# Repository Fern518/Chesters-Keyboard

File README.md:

# Chester's Keyboard
A custom TKL keyboard built for the *Hack Club Blueprint program*.

It functions as a miniature media dashboard: the display shows the current track (TO BE IMPLEMENTED), the knob controls volume, and the six keys can be bound to any shortcut.

## The Keyboard
Everything fits together using 4 M3 Bolts and Heatset inserts, one in each corner. 

It has 2 separate printed pieces. The base, where the PCB sits, and the top cover, which protects the PCB.

## PCB
My PCB was designed in KiCad. The rPi Pico is mounted on the bottom of the PCB between the home keys and arrow keys to make it as compact as possible.

Schematic:

PCB:

## BOM:
- 1x Case 
- 1x [Raspberry Pi Pico 2W](https://www.adafruit.com/pico?src=raspberrypi)
- 1x [0.91" 128x32 OLED Display](https://www.addicore.com/products/oled-display-128x32-0-91in-monochrome?variant=45759649120573)
- 1x [1N4148 Diodes - 100 Pack](https://www.adafruit.com/product/5099)
- 1x [EC11 Rotary Encoder](https://www.aliexpress.us/item/3256805924910339.html)
- 1x PCB (gerber files in pcb/)
- 89x [Cherry MX Switches](https://a.co/d/hjQgWfm)
- 89x [Keycaps](https://mechanicalkeyboards.com/products/tai-hao-104-key-pbt-double-shot-keycap-set-dark-greyblack)
- 1x [Keycap Stabilizers pack](https://divinikey.com/products/aeboards-staebies-v2-stabilizers?variant=40005101355073)
- 1x [Adafruit MCP23017 I2C GPIO Expander Breakout](https://www.adafruit.com/product/5346)
- 4x M3x5x4 Heatset inserts
- 4x M3x16mm SHCS Bolts

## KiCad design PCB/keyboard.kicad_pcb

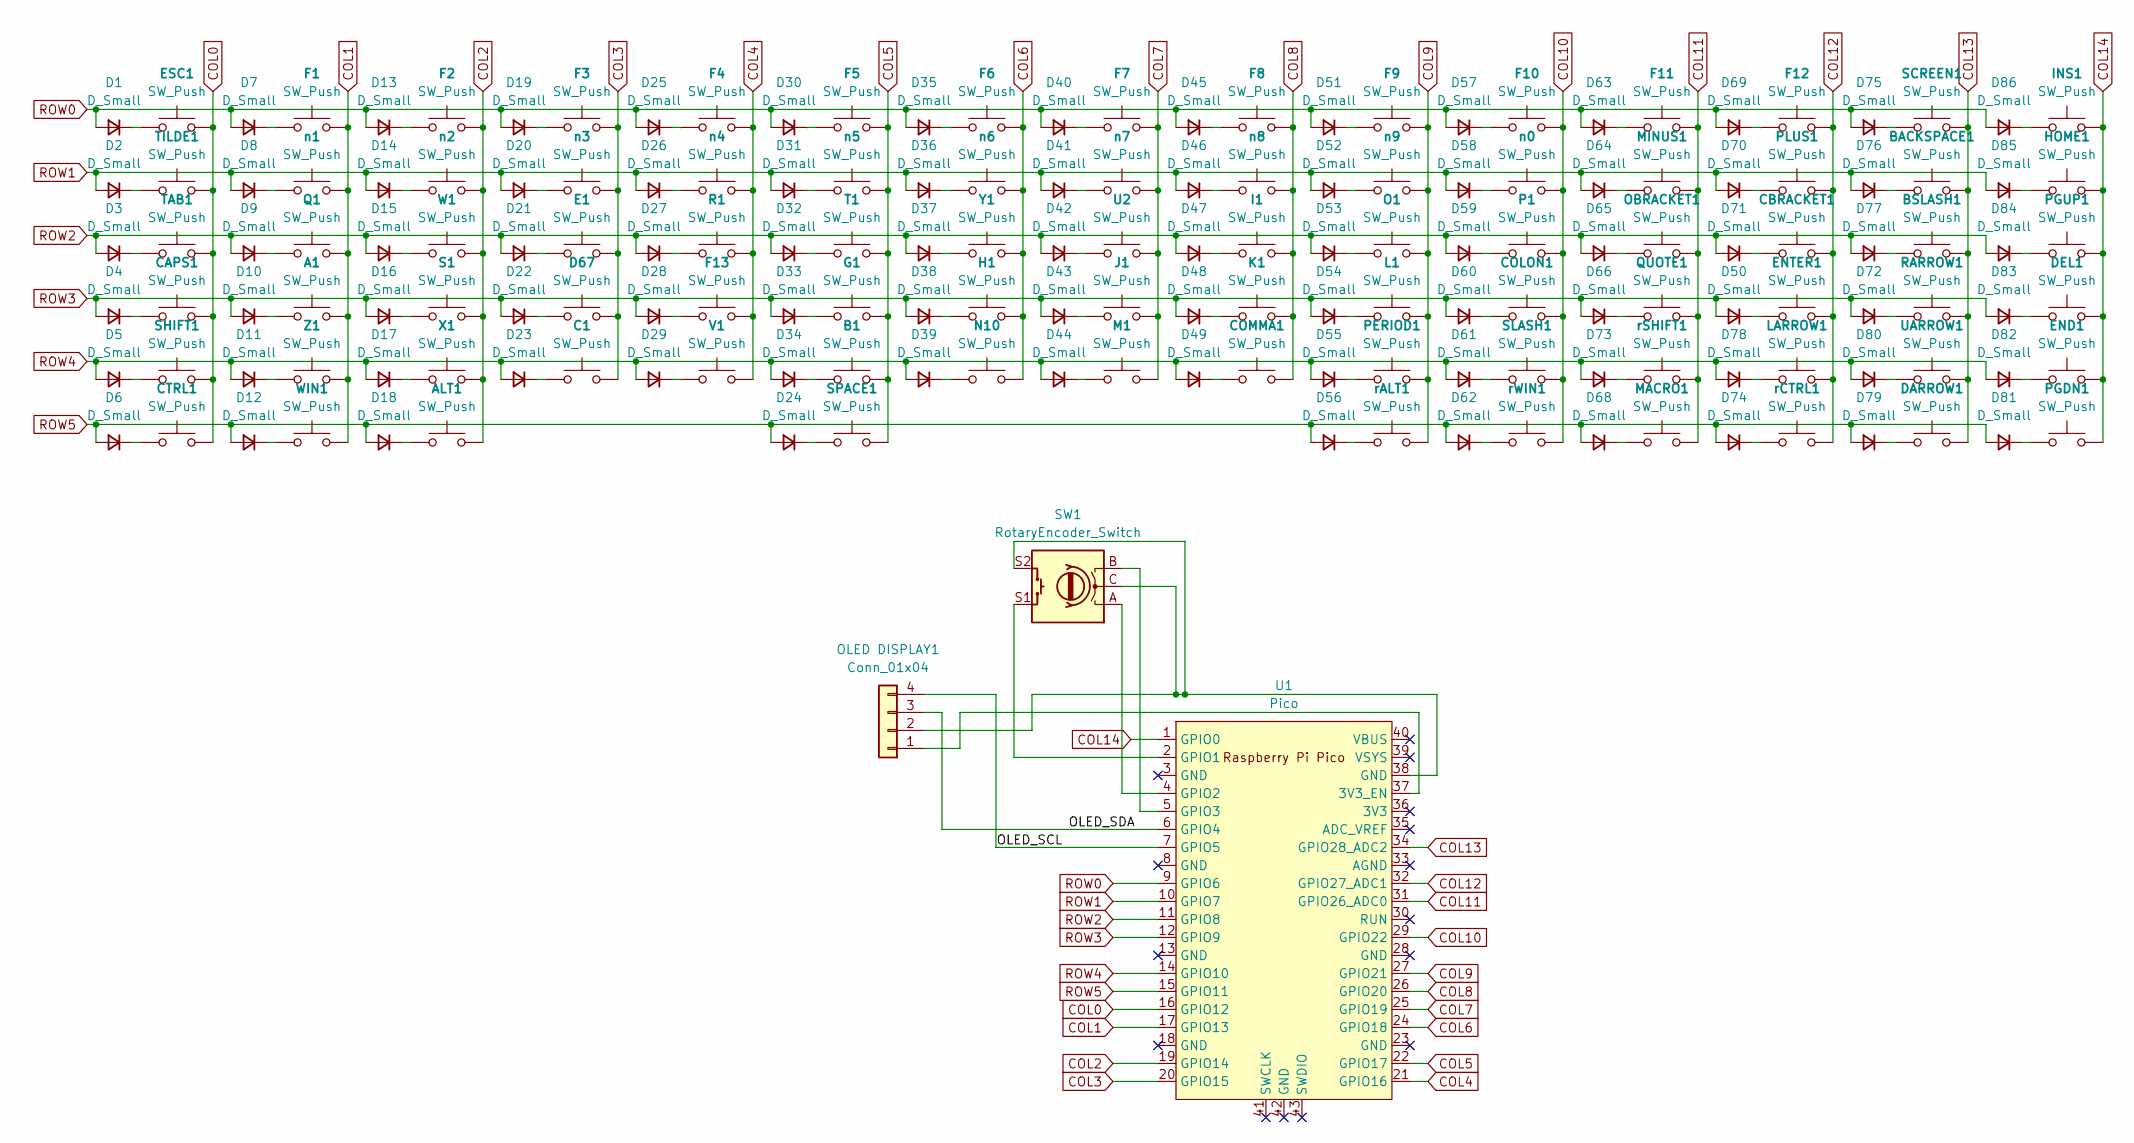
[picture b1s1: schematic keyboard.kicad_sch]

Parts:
A1: SW_Push; SW_Cherry_MX_1.00u_PCB
ALT1: SW_Push; SW_Cherry_MX_1.00u_PCB
B1: SW_Push; SW_Cherry_MX_1.00u_PCB
BACKSPACE1: SW_Push; SW_Cherry_MX_1.00u_PCB
BSLASH1: SW_Push; SW_Cherry_MX_1.00u_PCB
C1: SW_Push; SW_Cherry_MX_1.00u_PCB
CAPS1: SW_Push; SW_Cherry_MX_1.00u_PCB
CBRACKET1: SW_Push; SW_Cherry_MX_1.00u_PCB
COLON1: SW_Push; SW_Cherry_MX_1.00u_PCB
COMMA1: SW_Push; SW_Cherry_MX_1.00u_PCB
CTRL1: SW_Push; SW_Cherry_MX_1.00u_PCB
D1, D2, D3, D4, D5, D6, D7, D8, D9, D10, D11, D12, D13, D14, D15, D16, D17, D18, D19, D20, D21, D22, D23, D24, D25, D26, D27, D28, D29, D30, D31, D32, D33, D34, D35, D36, D37, D38, D39, D40, D41, D42, D43, D44, D45, D46, D47, D48, D49, D50, D51, D52, D53, D54, D55, D56, D57, D58, D59, D60, D61, D62, D63, D64, D65, D66, D68, D69, D70, D71, D72, D73, D74, D75, D76, D77, D78, D79, D80, D81, D82, D83, D84, D85, D86: D_Small; D_SOD-123
D67: SW_Push; SW_Cherry_MX_1.00u_PCB
DARROW1: SW_Push; SW_Cherry_MX_1.00u_PCB
DEL1: SW_Push; SW_Cherry_MX_1.00u_PCB
E1: SW_Push; SW_Cherry_MX_1.00u_PCB
END1: SW_Push; SW_Cherry_MX_1.00u_PCB
ENTER1: SW_Push; SW_Cherry_MX_1.00u_PCB
ESC1: SW_Push; SW_Cherry_MX_1.00u_PCB
F1, F2, F3, F4, F5, F6, F7, F8, F9, F10, F11, F12, F13: SW_Push; SW_Cherry_MX_1.00u_PCB
G1: SW_Push; SW_Cherry_MX_1.00u_PCB
H1: SW_Push; SW_Cherry_MX_1.00u_PCB
HOME1: SW_Push; SW_Cherry_MX_1.00u_PCB
I1: SW_Push; SW_Cherry_MX_1.00u_PCB
INS1: SW_Push; SW_Cherry_MX_1.00u_PCB
J1: SW_Push; SW_Cherry_MX_1.00u_PCB
K1: SW_Push; SW_Cherry_MX_1.00u_PCB
L1: SW_Push; SW_Cherry_MX_1.00u_PCB
LARROW1: SW_Push; SW_Cherry_MX_1.00u_PCB
M1: SW_Push; SW_Cherry_MX_1.00u_PCB
MACRO1: SW_Push; SW_Cherry_MX_1.00u_PCB
MINUS1: SW_Push; SW_Cherry_MX_1.00u_PCB
N10: SW_Push; SW_Cherry_MX_1.00u_PCB
O1: SW_Push; SW_Cherry_MX_1.00u_PCB
OBRACKET1: SW_Push; SW_Cherry_MX_1.00u_PCB
OLED DISPLAY1: Conn_01x04; PinHeader_1x04_P2.54mm_Vertical
P1: SW_Push; SW_Cherry_MX_1.00u_PCB
PERIOD1: SW_Push; SW_Cherry_MX_1.00u_PCB
PGDN1: SW_Push; SW_Cherry_MX_1.00u_PCB
PGUP1: SW_Push; SW_Cherry_MX_1.00u_PCB
PLUS1: SW_Push; SW_Cherry_MX_1.00u_PCB
Q1: SW_Push; SW_Cherry_MX_1.00u_PCB
QUOTE1: SW_Push; SW_Cherry_MX_1.00u_PCB
R1: SW_Push; SW_Cherry_MX_1.00u_PCB
RARROW1: SW_Push; SW_Cherry_MX_1.00u_PCB
S1: SW_Push; SW_Cherry_MX_1.00u_PCB
SCREEN1: SW_Push; SW_Cherry_MX_1.00u_PCB
SHIFT1: SW_Push; SW_Cherry_MX_1.00u_PCB
SLASH1: SW_Push; SW_Cherry_MX_1.00u_PCB
SPACE1: SW_Push; SW_Cherry_MX_1.00u_PCB
SW1: RotaryEncoder_Switch; RotaryEncoder_Alps_EC11E-Switch_Vertical_H20mm
T1: SW_Push; SW_Cherry_MX_1.00u_PCB
TAB1: SW_Push; SW_Cherry_MX_1.00u_PCB
TILDE1: SW_Push; SW_Cherry_MX_1.00u_PCB
U1: Pico; RPi_Pico_SMD_TH
U2: SW_Push; SW_Cherry_MX_1.00u_PCB
UARROW1: SW_Push; SW_Cherry_MX_1.00u_PCB
V1: SW_Push; SW_Cherry_MX_1.00u_PCB
W1: SW_Push; SW_Cherry_MX_1.00u_PCB
WIN1: SW_Push; SW_Cherry_MX_1.00u_PCB
X1: SW_Push; SW_Cherry_MX_1.00u_PCB
Y1: SW_Push; SW_Cherry_MX_1.00u_PCB
Z1: SW_Push; SW_Cherry_MX_1.00u_PCB
n0, n1, n2, n3, n4, n5, n6, n7, n8, n9: SW_Push; SW_Cherry_MX_1.00u_PCB
rALT1: SW_Push; SW_Cherry_MX_1.00u_PCB
rCTRL1: SW_Push; SW_Cherry_MX_1.00u_PCB
rSHIFT1: SW_Push; SW_Cherry_MX_1.00u_PCB
rWIN1: SW_Push; SW_Cherry_MX_1.00u_PCB

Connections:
/OLED_SCL: OLED DISPLAY1.4, U1.7 (GPIO5)
/OLED_SDA: OLED DISPLAY1.3, U1.6 (GPIO4)
COL0: CAPS1.2, CTRL1.2, ESC1.2, SHIFT1.2, TAB1.2, TILDE1.2, U1.16 (GPIO12)
COL1: A1.2, F1.2, Q1.2, U1.17 (GPIO13), WIN1.2, Z1.2, n1.2
COL2: ALT1.2, F2.2, S1.2, U1.19 (GPIO14), W1.2, X1.2, n2.2
COL3: C1.2, D67.2, E1.2, F3.2, U1.20 (GPIO15), n3.2
COL4: F4.2, F13.2, R1.2, U1.21 (GPIO16), V1.2, n4.2
COL5: B1.2, F5.2, G1.2, SPACE1.2, T1.2, U1.22 (GPIO17), n5.2
COL6: F6.2, H1.2, N10.2, U1.24 (GPIO18), Y1.2, n6.2
COL7: F7.2, J1.2, M1.2, U1.25 (GPIO19), U2.2, n7.2
COL8: COMMA1.2, F8.2, I1.2, K1.2, U1.26 (GPIO20), n8.2
COL9: F9.2, L1.2, O1.2, PERIOD1.2, U1.27 (GPIO21), n9.2, rALT1.2
COL10: COLON1.2, F10.2, P1.2, SLASH1.2, U1.29 (GPIO22), n0.2, rWIN1.2
COL11: F11.2, MACRO1.2, MINUS1.2, OBRACKET1.2, QUOTE1.2, U1.31 (GPIO26_ADC0), rSHIFT1.2
COL12: CBRACKET1.2, ENTER1.2, F12.2, LARROW1.2, PLUS1.2, U1.32 (GPIO27_ADC1), rCTRL1.2
COL13: BACKSPACE1.2, BSLASH1.2, DARROW1.2, RARROW1.2, SCREEN1.2, U1.34 (GPIO28_ADC2), UARROW1.2
COL14: DEL1.2, END1.2, HOME1.2, INS1.2, PGDN1.2, PGUP1.2, U1.1 (GPIO0)
unnamed: D1.1 (K), ESC1.1
unnamed: D2.1 (K), TILDE1.1
unnamed: D3.1 (K), TAB1.1
unnamed: CAPS1.1, D4.1 (K)
unnamed: D5.1 (K), SHIFT1.1
unnamed: CTRL1.1, D6.1 (K)
unnamed: D7.1 (K), F1.1
unnamed: D8.1 (K), n1.1
unnamed: D9.1 (K), Q1.1
unnamed: A1.1, D10.1 (K)
unnamed: D11.1 (K), Z1.1
unnamed: D12.1 (K), WIN1.1
unnamed: D13.1 (K), F2.1
unnamed: D14.1 (K), n2.1
unnamed: D15.1 (K), W1.1
unnamed: D16.1 (K), S1.1
unnamed: D17.1 (K), X1.1
unnamed: ALT1.1, D18.1 (K)
unnamed: D19.1 (K), F3.1
unnamed: D20.1 (K), n3.1
unnamed: D21.1 (K), E1.1
unnamed: D22.1 (K), D67.1
unnamed: C1.1, D23.1 (K)
unnamed: D24.1 (K), SPACE1.1
unnamed: D25.1 (K), F4.1
unnamed: D26.1 (K), n4.1
unnamed: D27.1 (K), R1.1
unnamed: D28.1 (K), F13.1
unnamed: D29.1 (K), V1.1
unnamed: D30.1 (K), F5.1
unnamed: D31.1 (K), n5.1
unnamed: D32.1 (K), T1.1
unnamed: D33.1 (K), G1.1
unnamed: B1.1, D34.1 (K)
unnamed: D35.1 (K), F6.1
unnamed: D36.1 (K), n6.1
unnamed: D37.1 (K), Y1.1
unnamed: D38.1 (K), H1.1
unnamed: D39.1 (K), N10.1
unnamed: D40.1 (K), F7.1
unnamed: D41.1 (K), n7.1
unnamed: D42.1 (K), U2.1
unnamed: D43.1 (K), J1.1
unnamed: D44.1 (K), M1.1
unnamed: D45.1 (K), F8.1
unnamed: D46.1 (K), n8.1
unnamed: D47.1 (K), I1.1
unnamed: D48.1 (K), K1.1
unnamed: COMMA1.1, D49.1 (K)
unnamed: D50.1 (K), ENTER1.1
unnamed: D51.1 (K), F9.1
unnamed: D52.1 (K), n9.1
unnamed: D53.1 (K), O1.1
unnamed: D54.1 (K), L1.1
unnamed: D55.1 (K), PERIOD1.1
unnamed: D56.1 (K), rALT1.1
unnamed: D57.1 (K), F10.1
unnamed: D58.1 (K), n0.1
unnamed: D59.1 (K), P1.1
unnamed: COLON1.1, D60.1 (K)
unnamed: D61.1 (K), SLASH1.1
unnamed: D62.1 (K), rWIN1.1
unnamed: D63.1 (K), F11.1
unnamed: D64.1 (K), MINUS1.1
unnamed: D65.1 (K), OBRACKET1.1
unnamed: D66.1 (K), QUOTE1.1
unnamed: D68.1 (K), MACRO1.1
unnamed: D69.1 (K), F12.1
unnamed: D70.1 (K), PLUS1.1
unnamed: CBRACKET1.1, D71.1 (K)
unnamed: D72.1 (K), RARROW1.1
unnamed: D73.1 (K), rSHIFT1.1
unnamed: D74.1 (K), rCTRL1.1
unnamed: D75.1 (K), SCREEN1.1
unnamed: BACKSPACE1.1, D76.1 (K)
unnamed: BSLASH1.1, D77.1 (K)
unnamed: D78.1 (K), LARROW1.1
unnamed: D79.1 (K), DARROW1.1
unnamed: D80.1 (K), UARROW1.1
unnamed: D81.1 (K), PGDN1.1
unnamed: D82.1 (K), END1.1
unnamed: D83.1 (K), DEL1.1
unnamed: D84.1 (K), PGUP1.1
unnamed: D85.1 (K), HOME1.1
unnamed: D86.1 (K), INS1.1
unnamed: OLED DISPLAY1.1, U1.37 (3V3_EN)
unnamed: OLED DISPLAY1.2, SW1.C, SW1.S2, U1.38 (GND)
unnamed: SW1.S1, U1.2 (GPIO1)
unnamed: SW1.A, U1.4 (GPIO2)
unnamed: SW1.B, U1.5 (GPIO3)
ROW0: D1.2 (A), D7.2 (A), D13.2 (A), D19.2 (A), D25.2 (A), D30.2 (A), D35.2 (A), D40.2 (A), D45.2 (A), D51.2 (A), D57.2 (A), D63.2 (A), D69.2 (A), D75.2 (A), D86.2 (A), U1.9 (GPIO6)
ROW1: D2.2 (A), D8.2 (A), D14.2 (A), D20.2 (A), D26.2 (A), D31.2 (A), D36.2 (A), D41.2 (A), D46.2 (A), D52.2 (A), D58.2 (A), D64.2 (A), D70.2 (A), D76.2 (A), D85.2 (A), U1.10 (GPIO7)
ROW2: D3.2 (A), D9.2 (A), D15.2 (A), D21.2 (A), D27.2 (A), D32.2 (A), D37.2 (A), D42.2 (A), D47.2 (A), D53.2 (A), D59.2 (A), D65.2 (A), D71.2 (A), D77.2 (A), D84.2 (A), U1.11 (GPIO8)
ROW3: D4.2 (A), D10.2 (A), D16.2 (A), D22.2 (A), D28.2 (A), D33.2 (A), D38.2 (A), D43.2 (A), D48.2 (A), D50.2 (A), D54.2 (A), D60.2 (A), D66.2 (A), D72.2 (A), D83.2 (A), U1.12 (GPIO9)
ROW4: D5.2 (A), D11.2 (A), D17.2 (A), D23.2 (A), D29.2 (A), D34.2 (A), D39.2 (A), D44.2 (A), D49.2 (A), D55.2 (A), D61.2 (A), D73.2 (A), D78.2 (A), D80.2 (A), D82.2 (A), U1.14 (GPIO10)
ROW5: D6.2 (A), D12.2 (A), D18.2 (A), D24.2 (A), D56.2 (A), D62.2 (A), D68.2 (A), D74.2 (A), D79.2 (A), D81.2 (A), U1.15 (GPIO11)

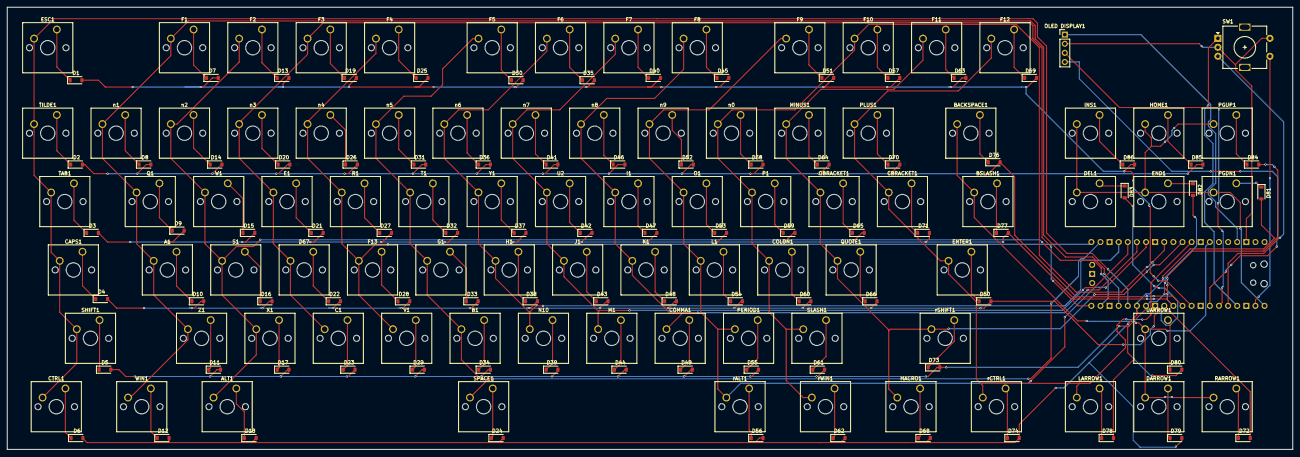
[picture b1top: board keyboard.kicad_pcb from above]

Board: 2 copper layers, 358.1 x 123.2 mm, 171 parts (1 on the bottom side), 112 nets.

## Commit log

2025-12-13 Created PCB Files
2025-12-13 Major PCB Updates (Read desc.)
    Since the last update, I designed an ANSI TKL based keyboard layout schematic in KiCad using a Raspberry Pi Pico 2W as the controller. I started by selecting and labeling usable GPIO pins on the Pico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
2025-12-13 Fixed a ton of ERC issues
2025-12-13 Fixed more issues
    Had to add weird number annotations to the end of each key to stop the ERC whining
2025-12-13 Reorganised keys to fit better
2025-12-13 Layed out key matrix
    This was extremely tedious and time consuming. I had to physically lay out all the keys in their correct positions on the PCB. I still haven't laid out the diodes, so that comes next. So far, I'm pre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
2025-12-13 Got rid of extra unnecessary key
2025-12-13 Moved diodes into position
2025-12-14 Wired rows and columns together
    I pretty much did the process of hooking each key and diode up to each row and collumn. I haven't attached them to the Raspberrry Pi Pico 2W yet, but that will come next.
2025-12-14 All rows connected
2025-12-14 Completed PCB
2025-12-14 Started work on case
2025-12-15 Fixed a bunch of key spacing issues
    I put in some more work on the case, then realized that if the keys are too close on the pcb, the keycaps wont fit (i was worried about larger keys like shift, and how far they should be spaced from 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
2025-12-16 Added top cover and PCB Adjustments
    moved home and arrow keys left to fit the standard ANSI grid
2025-12-17 Redid PCB bottom two rows
    Fixed spacing issues and rewired nodes
2025-12-19 Added keyboard top model and updated README
2025-12-26 Added basic firmware
2025-12-28 Added bom.csv and case with PCB image to readme
2025-12-31 added full board renders and gerber .zip
